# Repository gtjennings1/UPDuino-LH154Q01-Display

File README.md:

# UPDuino-LH154Q01-Display
Design to connect Lattice Ultraplus FPGA to LH154Q01 Display

UPDuino is a small maker board with a Lattice Ultraplus mobile FPGA.  The UPDuino LH154 Display Adapter Board provides the ability to attach a small 240x240 24-bit RGB display that has been used for many electronic devices including the iPod Nano (6th generation).  The FPGA can be used as a small graphics processor to deliver interactive graphics, bitmaps, fonts/text on the display.

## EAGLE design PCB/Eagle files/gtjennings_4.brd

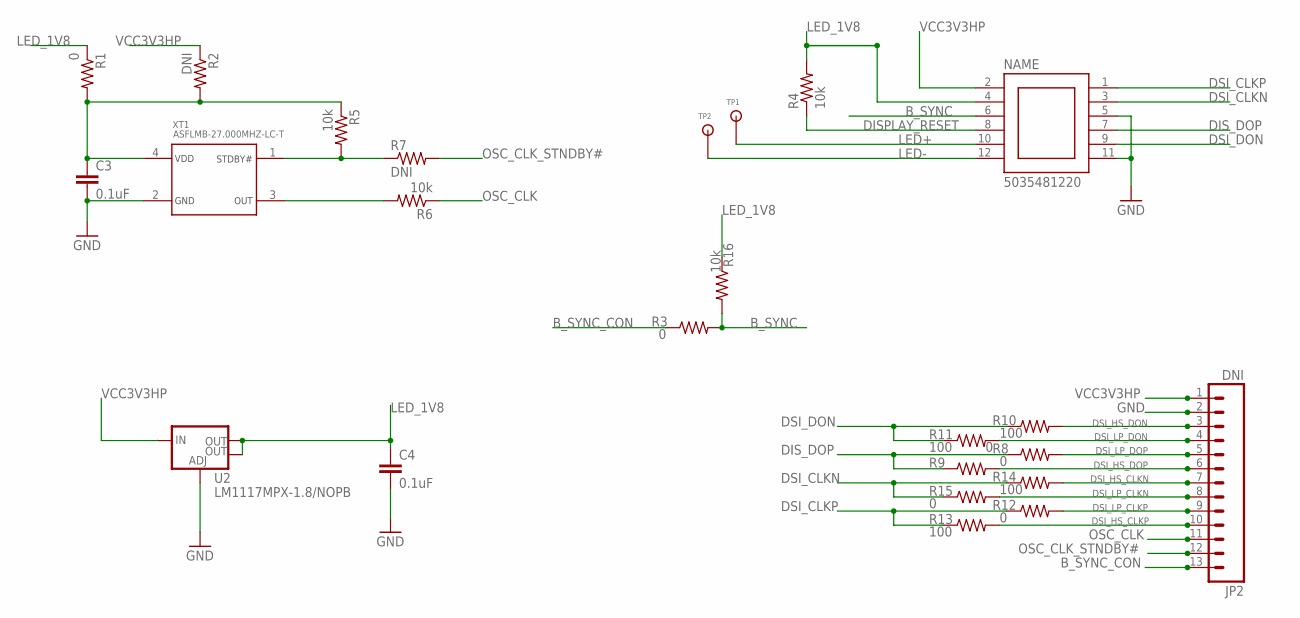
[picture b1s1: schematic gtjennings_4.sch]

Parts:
C3, C4: 0.1uF; 0402-CAP
JP1: 5035481220
JP2: DNI; 1X13
R1, R3, R8, R11, R12, R15: 0; 0402-RES
R2, R7: DNI; 0402-RES
R4, R5, R6, R16: 10k; 0402-RES
R9, R10, R13, R14: 100; 0402-RES
TP1, TP2: TP
U2: LM1117MPX-1.8/NOPB; SOT223
XT1: ASFLMB-27.000MHZ-LC-T

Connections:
B_SYNC: JP1.6, R3.2, R16.2
B_SYNC_CON: JP2.13, R3.1
DISPLAY_RESET: JP1.8, R4.1
DIS_DOP: JP1.7, R8.1, R9.1
DSI_CLKN: JP1.3, R14.1, R15.1
DSI_CLKP: JP1.1, R12.1, R13.1
DSI_DON: JP1.9, R10.1, R11.1
DSI_HS_CLKN: JP2.7, R14.2
DSI_HS_CLKP: JP2.10, R13.2
DSI_HS_DON: JP2.3, R10.2
DSI_HS_DOP: JP2.6, R9.2
DSI_LP_CLKN: JP2.8, R15.2
DSI_LP_CLKP: JP2.9, R12.2
DSI_LP_DON: JP2.4, R11.2
DSI_LP_DOP: JP2.5, R8.2
GND: C3.2, C4.2, JP1.5, JP1.11, JP2.2, U2.1 (ADJ), XT1.2
LED+: JP1.10, TP1.1
LED-: JP1.12, TP2.1
LED_1V8: C4.1, JP1.4, R1.1, R4.2, R16.1, U2.2 (OUT), U2.4 (OUT)
unnamed: R5.2, R7.1, XT1.1
OSC_CLK: JP2.11, R6.1
OSC_CLK6: R6.2, XT1.3
OSC_CLK_STNDBY#: JP2.12, R7.2
OSC_PWR: C3.1, R1.2, R2.2, R5.1, XT1.4
VCC3V3HP: JP1.2, JP2.1, R2.1, U2.3 (IN)

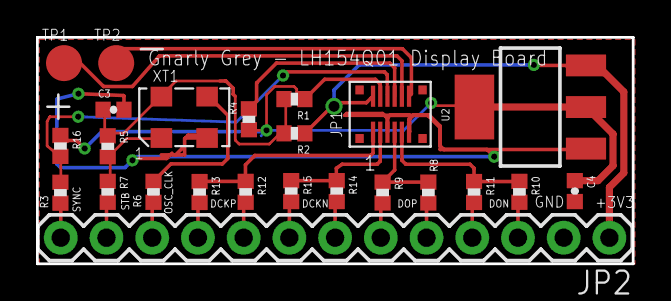
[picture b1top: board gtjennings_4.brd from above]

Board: 2 copper layers, 33.1 x 12.6 mm, 24 parts (0 on the bottom side), 25 nets.

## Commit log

2018-06-12 Register map for GPU design
2018-07-25 added ip documentation with register info

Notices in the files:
parts and their libraries:
SparkFun-Resistors: Licensing: Creative Commons ShareAlike 4.0 International - https://creativecommons.org/licenses/by-sa/4.0
